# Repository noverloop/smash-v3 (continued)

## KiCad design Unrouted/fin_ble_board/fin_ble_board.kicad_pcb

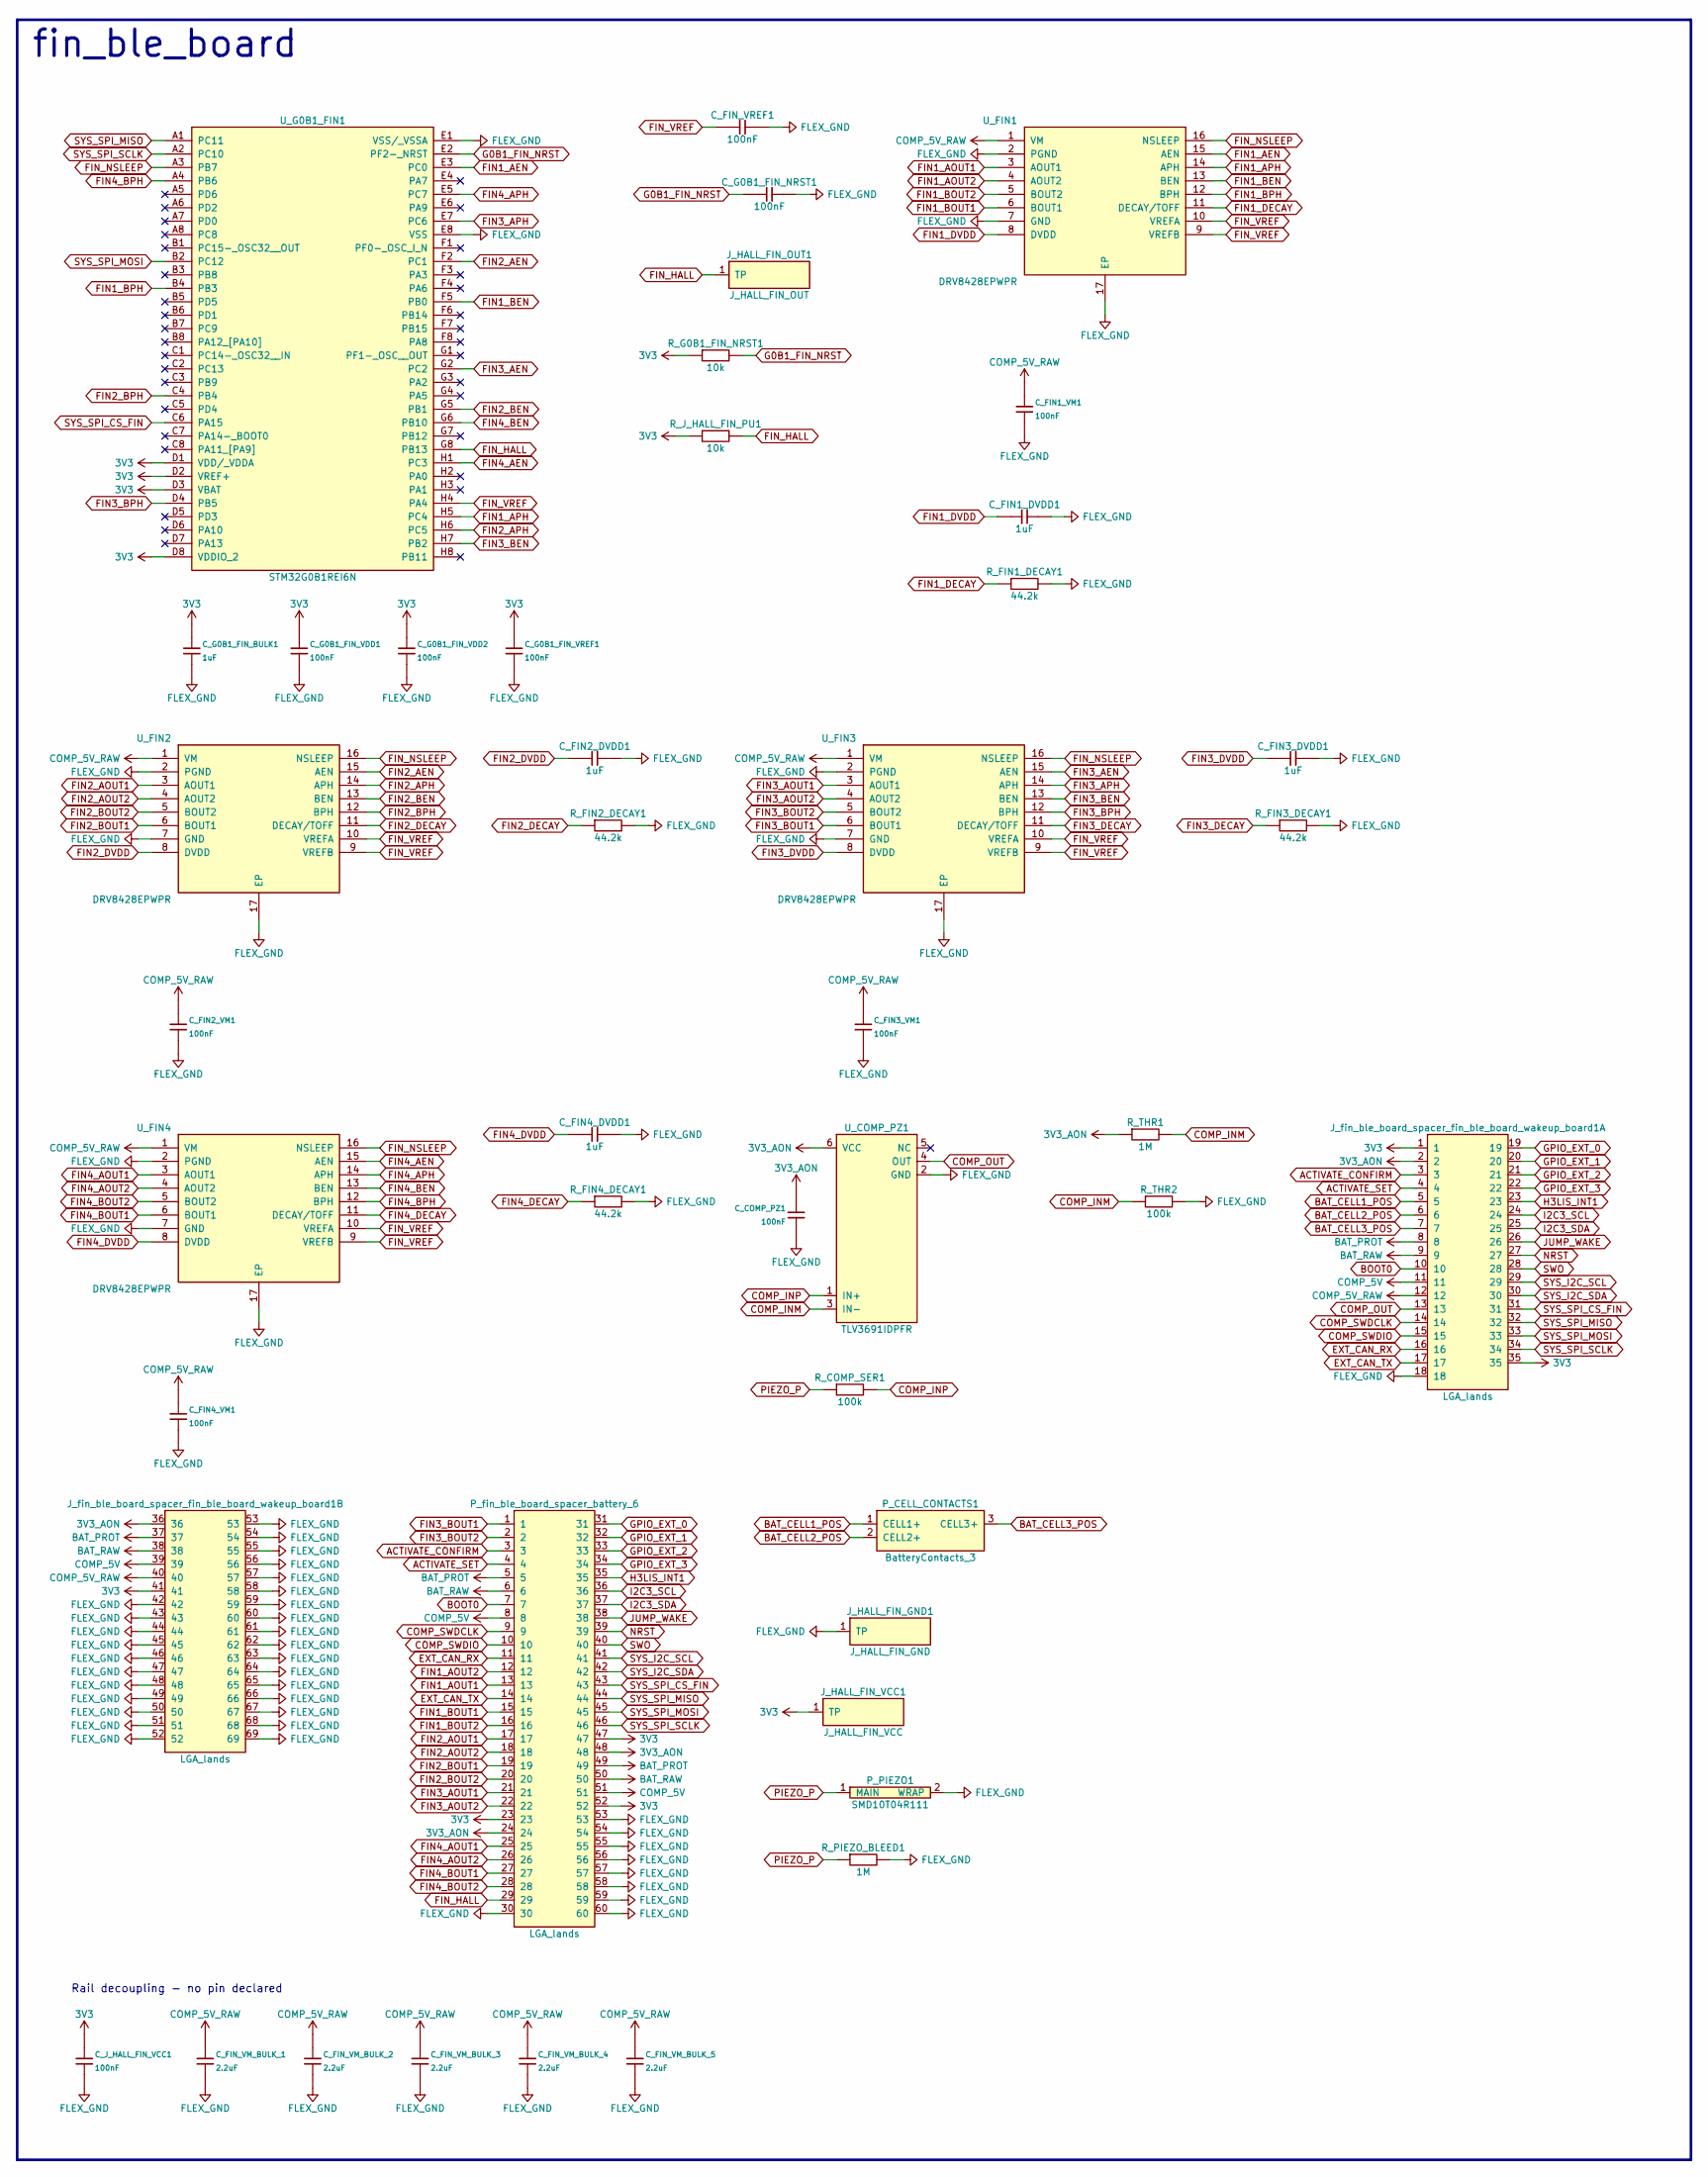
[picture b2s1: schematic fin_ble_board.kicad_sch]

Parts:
C_COMP_PZ1: 100nF; Capacitor_SMD_C_0402_1005Metric; MPN C0402 X7R 100nF
C_FIN1_DVDD1, C_FIN2_DVDD1, C_FIN3_DVDD1, C_FIN4_DVDD1: 1uF; Capacitor_SMD_C_0805_2012Metric; MPN C-Series MIL-PRF-32535 X7R 0805 1uF
C_FIN1_VM1, C_FIN2_VM1, C_FIN3_VM1, C_FIN4_VM1: 100nF; Capacitor_SMD_C_0402_1005Metric; MPN C0402 X7R 100nF
C_FIN_VM_BULK_1, C_FIN_VM_BULK_2, C_FIN_VM_BULK_3, C_FIN_VM_BULK_4, C_FIN_VM_BULK_5: 2.2uF; Capacitor_SMD_C_0603_1608Metric; MPN C-Series MIL-PRF-32535 X7R 0603 2.2uF
C_FIN_VREF1: 100nF; Capacitor_SMD_C_0402_1005Metric; MPN C0402 X7R 100nF
C_G0B1_FIN_BULK1: 1uF; Capacitor_SMD_C_0805_2012Metric; MPN C-Series MIL-PRF-32535 X7R 0805 1uF
C_G0B1_FIN_NRST1, C_G0B1_FIN_VDD1, C_G0B1_FIN_VDD2, C_G0B1_FIN_VREF1: 100nF; Capacitor_SMD_C_0402_1005Metric; MPN C0402 X7R 100nF
C_J_HALL_FIN_VCC1: 100nF; Capacitor_SMD_C_0402_1005Metric; MPN C0402 X7R 100nF
J_HALL_FIN_GND1: J_HALL_FIN_GND; Pogo_Pad_D2.0mm
J_HALL_FIN_OUT1: J_HALL_FIN_OUT; Pogo_Pad_D2.0mm
J_HALL_FIN_VCC1: J_HALL_FIN_VCC; Pogo_Pad_D2.0mm
J_fin_ble_board_spacer_fin_ble_board_wakeup_board1: LGA_lands; J_fin_ble_board_spacer_fin_ble_board_wakeup_board; MPN LGA_lands
P_CELL_CONTACTS1: BatteryContacts_3; MPN BatteryContacts_3
P_PIEZO1: SMD10T04R111; PiezoDisc_SMD10T04R111; MPN SMD10T04R111
P_fin_ble_board_spacer_battery_6: LGA_lands; P_fin_ble_board_spacer_battery_6; MPN LGA_lands
R_COMP_SER1: 100k; Resistor_SMD_R_0402_1005Metric; MPN CRCW0402 100k 1% e3
R_FIN1_DECAY1, R_FIN2_DECAY1, R_FIN3_DECAY1, R_FIN4_DECAY1: 44.2k; Resistor_SMD_R_0402_1005Metric; MPN CRCW0402 44.2k 1% e3
R_G0B1_FIN_NRST1: 10k; Resistor_SMD_R_0402_1005Metric; MPN CRCW0402 10k 1% e3
R_J_HALL_FIN_PU1: 10k; Resistor_SMD_R_0402_1005Metric; MPN CRCW0402 10k 1% e3
R_PIEZO_BLEED1: 1M; Resistor_SMD_R_0402_1005Metric; MPN CRCW0402 1M 1% e3
R_THR1: 1M; Resistor_SMD_R_0402_1005Metric; MPN CRCW0402 1M 1% e3
R_THR2: 100k; Resistor_SMD_R_0402_1005Metric; MPN CRCW0402 100k 1% e3
U_COMP_PZ1: TLV3691IDPFR; DPF0006A; MPN TLV3691IDPFR
U_FIN1, U_FIN2, U_FIN3, U_FIN4: DRV8428EPWPR; SOP65P640X120-17N; MPN DRV8428EPWPR
U_G0B1_FIN1: STM32G0B1REI6N; BGA64C50P8X8_500X500X60; MPN STM32G0B1REI6N

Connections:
3V3: C_G0B1_FIN_BULK1.1, C_G0B1_FIN_VDD1.1, C_G0B1_FIN_VDD2.1, C_G0B1_FIN_VREF1.1, C_J_HALL_FIN_VCC1.1, J_HALL_FIN_VCC1.1, J_fin_ble_board_spacer_fin_ble_board_wa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.1, J_fin_ble_board_spacer_fin_ble_board_wa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.35, J_fin_ble_board_spacer_fin_ble_board_wa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.41, P_fin_ble_board_spacer_battery_6.23, P_fin_ble_board_spacer_battery_6.47, P_fin_ble_board_spacer_battery_6.52, R_G0B1_FIN_NRST1.1, R_J_HALL_FIN_PU1.1, U_G0B1_FIN1.D1 (VDD/_VDDA), U_G0B1_FIN1.D2 (VREF+), U_G0B1_FIN1.D3 (VBAT), U_G0B1_FIN1.D8 (VDDIO_2)
3V3_AON: C_COMP_PZ1.1, J_fin_ble_board_spacer_fin_ble_board_wa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.2, J_fin_ble_board_spacer_fin_ble_board_wa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.36, P_fin_ble_board_spacer_battery_6.24, P_fin_ble_board_spacer_battery_6.48, R_THR1.1, U_COMP_PZ1.6 (VCC)
ACTIVATE_CONFIRM: J_fin_ble_board_spacer_fin_ble_board_wa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.3, P_fin_ble_board_spacer_battery_6.3
ACTIVATE_SET: J_fin_ble_board_spacer_fin_ble_board_wa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.4, P_fin_ble_board_spacer_battery_6.4
BAT_CELL1_POS: J_fin_ble_board_spacer_fin_ble_board_wa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.5, P_CELL_CONTACTS1.1 (CELL1+)
BAT_CELL2_POS: J_fin_ble_board_spacer_fin_ble_board_wa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.6, P_CELL_CONTACTS1.2 (CELL2+)
BAT_CELL3_POS: J_fin_ble_board_spacer_fin_ble_board_wa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.7, P_CELL_CONTACTS1.3 (CELL3+)
BAT_PROT: J_fin_ble_board_spacer_fin_ble_board_wa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.8, J_fin_ble_board_spacer_fin_ble_board_wa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.37, P_fin_ble_board_spacer_battery_6.5, P_fin_ble_board_spacer_battery_6.49
BAT_RAW: J_fin_ble_board_spacer_fin_ble_board_wa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.9, J_fin_ble_board_spacer_fin_ble_board_wa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.38, P_fin_ble_board_spacer_battery_6.6, P_fin_ble_board_spacer_battery_6.50
BOOT0: J_fin_ble_board_spacer_fin_ble_board_wa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.10, P_fin_ble_board_spacer_battery_6.7
COMP_5V: J_fin_ble_board_spacer_fin_ble_board_wa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.11, J_fin_ble_board_spacer_fin_ble_board_wa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.39, P_fin_ble_board_spacer_battery_6.8, P_fin_ble_board_spacer_battery_6.51
COMP_5V_RAW: C_FIN1_VM1.1, C_FIN2_VM1.1, C_FIN3_VM1.1, C_FIN4_VM1.1, C_FIN_VM_BULK_1.1, C_FIN_VM_BULK_2.1, C_FIN_VM_BULK_3.1, C_FIN_VM_BULK_4.1, C_FIN_VM_BULK_5.1, J_fin_ble_board_spacer_fin_ble_board_wa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.12, J_fin_ble_board_spacer_fin_ble_board_wa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.40, U_FIN1.1 (VM), U_FIN2.1 (VM), U_FIN3.1 (VM), U_FIN4.1 (VM)
COMP_INM: R_THR1.2, R_THR2.1, U_COMP_PZ1.3 (IN-)
COMP_INP: R_COMP_SER1.2, U_COMP_PZ1.1 (IN+)
COMP_OUT: J_fin_ble_board_spacer_fin_ble_board_wa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.13, U_COMP_PZ1.4 (OUT)
COMP_SWDCLK: J_fin_ble_board_spacer_fin_ble_board_wa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.14, P_fin_ble_board_spacer_battery_6.9
COMP_SWDIO: J_fin_ble_board_spacer_fin_ble_board_wa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.15, P_fin_ble_board_spacer_battery_6.10
EXT_CAN_RX: J_fin_ble_board_spacer_fin_ble_board_wa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.16, P_fin_ble_board_spacer_battery_6.11
EXT_CAN_TX: J_fin_ble_board_spacer_fin_ble_board_wa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.17, P_fin_ble_board_spacer_battery_6.14
FIN1_AEN: U_FIN1.15 (AEN), U_G0B1_FIN1.E3 (PC0)
FIN1_AOUT1: P_fin_ble_board_spacer_battery_6.13, U_FIN1.3 (AOUT1)
FIN1_AOUT2: P_fin_ble_board_spacer_battery_6.12, U_FIN1.4 (AOUT2)
FIN1_APH: U_FIN1.14 (APH), U_G0B1_FIN1.H5 (PC4)
FIN1_BEN: U_FIN1.13 (BEN), U_G0B1_FIN1.F5 (PB0)
FIN1_BOUT1: P_fin_ble_board_spacer_battery_6.15, U_FIN1.6 (BOUT1)
FIN1_BOUT2: P_fin_ble_board_spacer_battery_6.16, U_FIN1.5 (BOUT2)
FIN1_BPH: U_FIN1.12 (BPH), U_G0B1_FIN1.B4 (PB3)
FIN1_DECAY: R_FIN1_DECAY1.1, U_FIN1.11 (DECAY/TOFF)
FIN1_DVDD: C_FIN1_DVDD1.1, U_FIN1.8 (DVDD)
FIN2_AEN: U_FIN2.15 (AEN), U_G0B1_FIN1.F2 (PC1)
FIN2_AOUT1: P_fin_ble_board_spacer_battery_6.17, U_FIN2.3 (AOUT1)
FIN2_AOUT2: P_fin_ble_board_spacer_battery_6.18, U_FIN2.4 (AOUT2)
FIN2_APH: U_FIN2.14 (APH), U_G0B1_FIN1.H6 (PC5)
FIN2_BEN: U_FIN2.13 (BEN), U_G0B1_FIN1.G5 (PB1)
FIN2_BOUT1: P_fin_ble_board_spacer_battery_6.19, U_FIN2.6 (BOUT1)
FIN2_BOUT2: P_fin_ble_board_spacer_battery_6.20, U_FIN2.5 (BOUT2)
FIN2_BPH: U_FIN2.12 (BPH), U_G0B1_FIN1.C4 (PB4)
FIN2_DECAY: R_FIN2_DECAY1.1, U_FIN2.11 (DECAY/TOFF)
FIN2_DVDD: C_FIN2_DVDD1.1, U_FIN2.8 (DVDD)
FIN3_AEN: U_FIN3.15 (AEN), U_G0B1_FIN1.G2 (PC2)
FIN3_AOUT1: P_fin_ble_board_spacer_battery_6.21, U_FIN3.3 (AOUT1)
FIN3_AOUT2: P_fin_ble_board_spacer_battery_6.22, U_FIN3.4 (AOUT2)
FIN3_APH: U_FIN3.14 (APH), U_G0B1_FIN1.E7 (PC6)
FIN3_BEN: U_FIN3.13 (BEN), U_G0B1_FIN1.H7 (PB2)
FIN3_BOUT1: P_fin_ble_board_spacer_battery_6.1, U_FIN3.6 (BOUT1)
FIN3_BOUT2: P_fin_ble_board_spacer_battery_6.2, U_FIN3.5 (BOUT2)
FIN3_BPH: U_FIN3.12 (BPH), U_G0B1_FIN1.D4 (PB5)
FIN3_DECAY: R_FIN3_DECAY1.1, U_FIN3.11 (DECAY/TOFF)
FIN3_DVDD: C_FIN3_DVDD1.1, U_FIN3.8 (DVDD)
FIN4_AEN: U_FIN4.15 (AEN), U_G0B1_FIN1.H1 (PC3)
FIN4_AOUT1: P_fin_ble_board_spacer_battery_6.25, U_FIN4.3 (AOUT1)
FIN4_AOUT2: P_fin_ble_board_spacer_battery_6.26, U_FIN4.4 (AOUT2)
FIN4_APH: U_FIN4.14 (APH), U_G0B1_FIN1.E5 (PC7)
FIN4_BEN: U_FIN4.13 (BEN), U_G0B1_FIN1.G6 (PB10)
FIN4_BOUT1: P_fin_ble_board_spacer_battery_6.27, U_FIN4.6 (BOUT1)
FIN4_BOUT2: P_fin_ble_board_spacer_battery_6.28, U_FIN4.5 (BOUT2)
FIN4_BPH: U_FIN4.12 (BPH), U_G0B1_FIN1.A4 (PB6)
FIN4_DECAY: R_FIN4_DECAY1.1, U_FIN4.11 (DECAY/TOFF)
FIN4_DVDD: C_FIN4_DVDD1.1, U_FIN4.8 (DVDD)
FIN_HALL: J_HALL_FIN_OUT1.1, P_fin_ble_board_spacer_battery_6.29, R_J_HALL_FIN_PU1.2, U_G0B1_FIN1.G8 (PB13)
FIN_NSLEEP: U_FIN1.16 (NSLEEP), U_FIN2.16 (NSLEEP), U_FIN3.16 (NSLEEP), U_FIN4.16 (NSLEEP), U_G0B1_FIN1.A3 (PB7)
FIN_VREF: C_FIN_VREF1.1, U_FIN1.9 (VREFB), U_FIN1.10 (VREFA), U_FIN2.9 (VREFB), U_FIN2.10 (VREFA), U_FIN3.9 (VREFB), U_FIN3.10 (VREFA), U_FIN4.9 (VREFB), U_FIN4.10 (VREFA), U_G0B1_FIN1.H4 (PA4)
FLEX_GND: C_COMP_PZ1.2, C_FIN1_DVDD1.2, C_FIN1_VM1.2, C_FIN2_DVDD1.2, C_FIN2_VM1.2, C_FIN3_DVDD1.2, C_FIN3_VM1.2, C_FIN4_DVDD1.2, C_FIN4_VM1.2, C_FIN_VM_BULK_1.2, C_FIN_VM_BULK_2.2, C_FIN_VM_BULK_3.2, C_FIN_VM_BULK_4.2, C_FIN_VM_BULK_5.2, C_FIN_VREF1.2, C_G0B1_FIN_BULK1.2, C_G0B1_FIN_NRST1.2, C_G0B1_FIN_VDD1.2, C_G0B1_FIN_VDD2.2, C_G0B1_FIN_VREF1.2, C_J_HALL_FIN_VCC1.2, J_HALL_FIN_GND1.1, J_fin_ble_board_spacer_fin_ble_board_wa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.18, J_fin_ble_board_spacer_fin_ble_board_wa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.42, J_fin_ble_board_spacer_fin_ble_board_wa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.43, J_fin_ble_board_spacer_fin_ble_board_wa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.44, J_fin_ble_board_spacer_fin_ble_board_wa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.45, J_fin_ble_board_spacer_fin_ble_board_wa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.46, J_fin_ble_board_spacer_fin_ble_board_wa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.47, J_fin_ble_board_spacer_fin_ble_board_wa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.48, J_fin_ble_board_spacer_fin_ble_board_wa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.49, J_fin_ble_board_spacer_fin_ble_board_wa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.50, J_fin_ble_board_spacer_fin_ble_board_wa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.51, J_fin_ble_board_spacer_fin_ble_board_wa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.52, J_fin_ble_board_spacer_fin_ble_board_wa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.53, J_fin_ble_board_spacer_fin_ble_board_wa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.54, J_fin_ble_board_spacer_fin_ble_board_wa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.55, J_fin_ble_board_spacer_fin_ble_board_wa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.56, J_fin_ble_board_spacer_fin_ble_board_wa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.57, J_fin_ble_board_spacer_fin_ble_board_wa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.58, J_fin_ble_board_spacer_fin_ble_board_wa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.59, J_fin_ble_board_spacer_fin_ble_board_wa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.60, J_fin_ble_board_spacer_fin_ble_board_wa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.61, J_fin_ble_board_spacer_fin_ble_board_wa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.62, J_fin_ble_board_spacer_fin_ble_board_wa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.63, J_fin_ble_board_spacer_fin_ble_board_wa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.64, J_fin_ble_board_spacer_fin_ble_board_wa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.65, J_fin_ble_board_spacer_fin_ble_board_wa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.66, J_fin_ble_board_spacer_fin_ble_board_wa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.67, J_fin_ble_board_spacer_fin_ble_board_wa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.68, J_fin_ble_board_spacer_fin_ble_board_wa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.69, P_PIEZO1.2 (WRAP), P_fin_ble_board_spacer_battery_6.30, P_fin_ble_board_spacer_battery_6.53, P_fin_ble_board_spacer_battery_6.54, P_fin_ble_board_spacer_battery_6.55, P_fin_ble_board_spacer_battery_6.56, P_fin_ble_board_spacer_battery_6.57, P_fin_ble_board_spacer_battery_6.58, P_fin_ble_board_spacer_battery_6.59, P_fin_ble_board_spacer_battery_6.60, R_FIN1_DECAY1.2, R_FIN2_DECAY1.2, R_FIN3_DECAY1.2, R_FIN4_DECAY1.2, R_PIEZO_BLEED1.2, R_THR2.2, U_COMP_PZ1.2 (GND), U_FIN1.2 (PGND), U_FIN1.7 (GND), U_FIN1.17 (EP), U_FIN2.2 (PGND), U_FIN2.7 (GND), U_FIN2.17 (EP), U_FIN3.2 (PGND), U_FIN3.7 (GND), U_FIN3.17 (EP), U_FIN4.2 (PGND), U_FIN4.7 (GND), U_FIN4.17 (EP), U_G0B1_FIN1.E1 (VSS/_VSSA), U_G0B1_FIN1.E8 (VSS)
G0B1_FIN_NRST: C_G0B1_FIN_NRST1.1, R_G0B1_FIN_NRST1.2, U_G0B1_FIN1.E2 (PF2-_NRST)
GPIO_EXT_0: J_fin_ble_board_spacer_fin_ble_board_wa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.19, P_fin_ble_board_spacer_battery_6.31
GPIO_EXT_1: J_fin_ble_board_spacer_fin_ble_board_wa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.20, P_fin_ble_board_spacer_battery_6.32
GPIO_EXT_2: J_fin_ble_board_spacer_fin_ble_board_wa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.21, P_fin_ble_board_spacer_battery_6.33
GPIO_EXT_3: J_fin_ble_board_spacer_fin_ble_board_wa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.22, P_fin_ble_board_spacer_battery_6.34
H3LIS_INT1: J_fin_ble_board_spacer_fin_ble_board_wa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.23, P_fin_ble_board_spacer_battery_6.35
I2C3_SCL: J_fin_ble_board_spacer_fin_ble_board_wa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.24, P_fin_ble_board_spacer_battery_6.36
I2C3_SDA: J_fin_ble_board_spacer_fin_ble_board_wa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.25, P_fin_ble_board_spacer_battery_6.37
JUMP_WAKE: J_fin_ble_board_spacer_fin_ble_board_wa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.26, P_fin_ble_board_spacer_battery_6.38
NRST: J_fin_ble_board_spacer_fin_ble_board_wa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.27, P_fin_ble_board_spacer_battery_6.39
PIEZO_P: P_PIEZO1.1 (MAIN), R_COMP_SER1.1, R_PIEZO_BLEED1.1
SWO: J_fin_ble_board_spacer_fin_ble_board_wa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.28, P_fin_ble_board_spacer_battery_6.40
SYS_I2C_SCL: J_fin_ble_board_spacer_fin_ble_board_wa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.29, P_fin_ble_board_spacer_battery_6.41
SYS_I2C_SDA: J_fin_ble_board_spacer_fin_ble_board_wa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.30, P_fin_ble_board_spacer_battery_6.42
SYS_SPI_CS_FIN: J_fin_ble_board_spacer_fin_ble_board_wa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.31, P_fin_ble_board_spacer_battery_6.43, U_G0B1_FIN1.C6 (PA15)
SYS_SPI_MISO: J_fin_ble_board_spacer_fin_ble_board_wa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.32, P_fin_ble_board_spacer_battery_6.44, U_G0B1_FIN1.A1 (PC11)
SYS_SPI_MOSI: J_fin_ble_board_spacer_fin_ble_board_wa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.33, P_fin_ble_board_spacer_battery_6.45, U_G0B1_FIN1.B2 (PC12)
SYS_SPI_SCLK: J_fin_ble_board_spacer_fin_ble_board_wa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.34, P_fin_ble_board_spacer_battery_6.46, U_G0B1_FIN1.A2 (PC10)

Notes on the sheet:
fin_ble_board
Rail decoupling - no pin declared

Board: 14 copper layers, 46 parts (31 on the bottom side), 81 nets, no tracks yet.

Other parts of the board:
MH1, MH2: smash_mech_potting

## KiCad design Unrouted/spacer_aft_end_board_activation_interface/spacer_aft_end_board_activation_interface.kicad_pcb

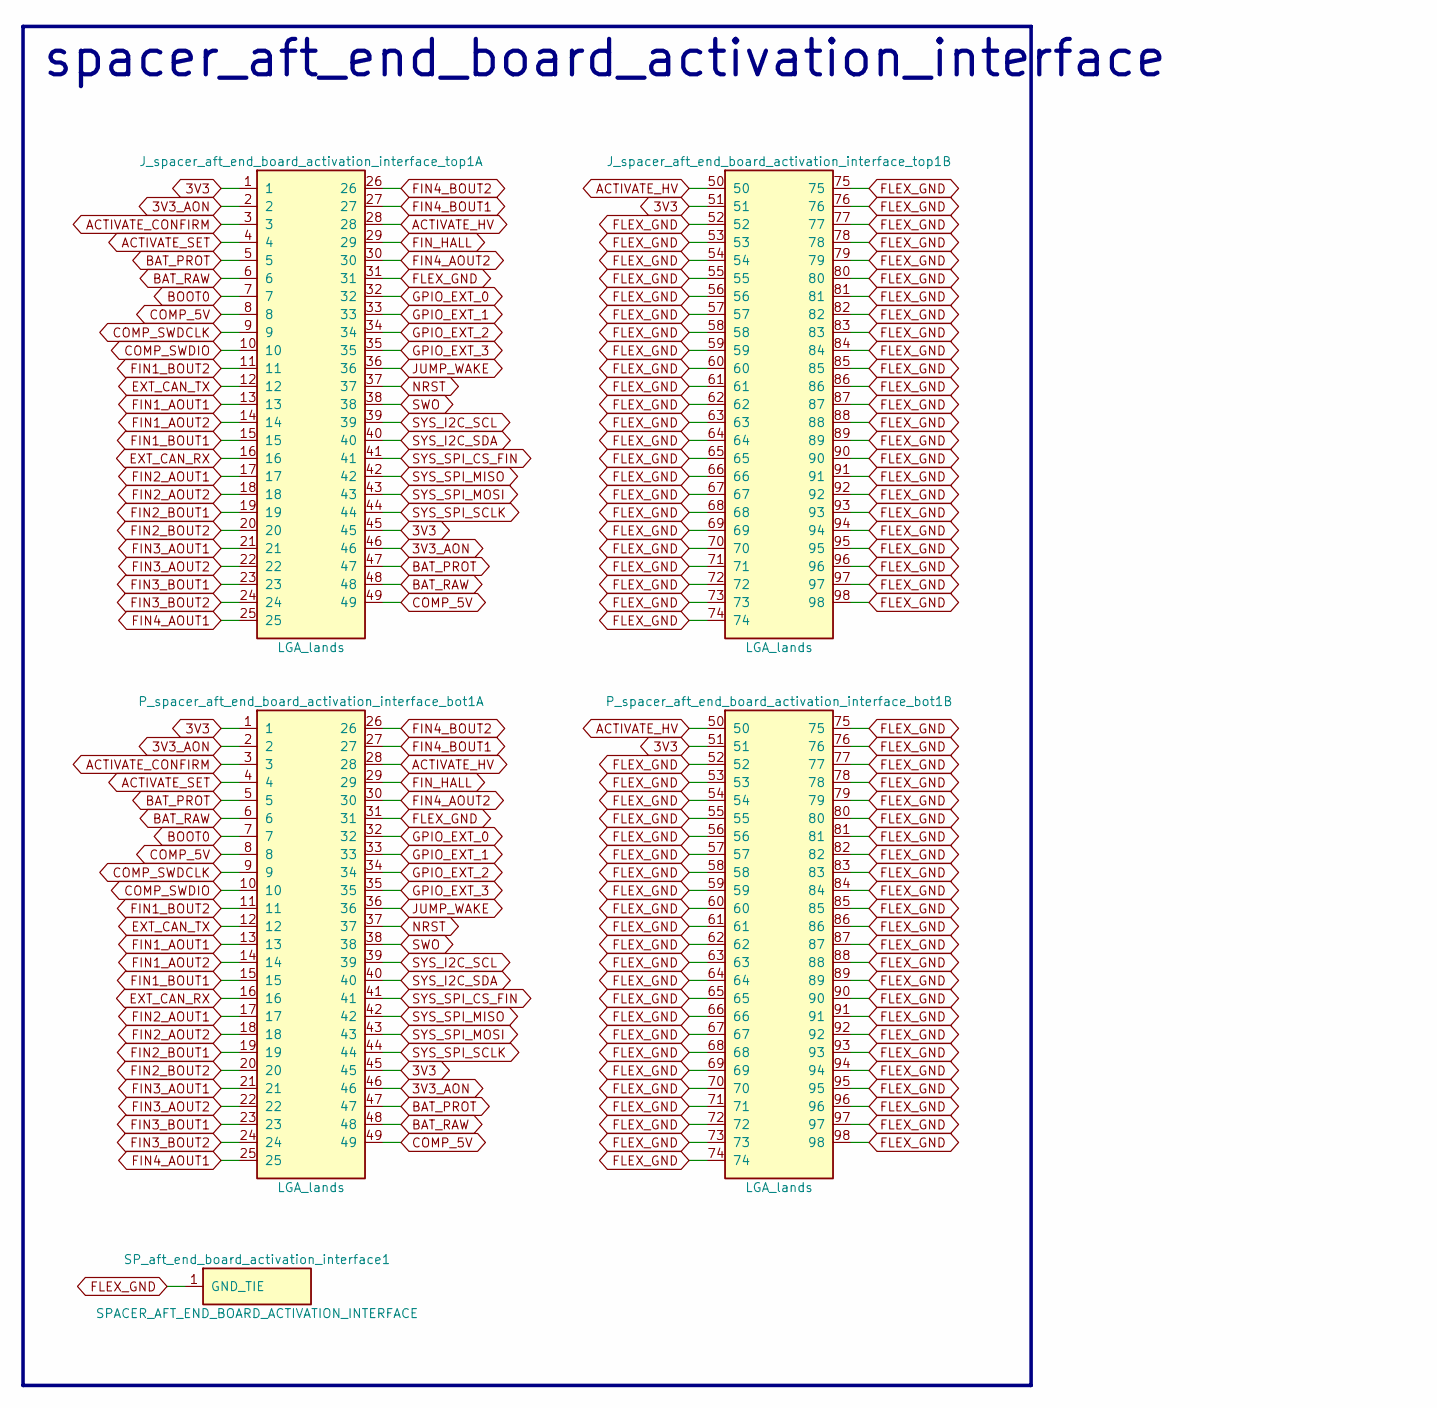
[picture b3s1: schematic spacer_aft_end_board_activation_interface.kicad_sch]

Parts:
J_spacer_aft_end_board_activation_interface_top1: LGA_lands; J_spacer_aft_end_board_activation_interface_top; MPN LGA_lands
P_spacer_aft_end_board_activation_interface_bot1: LGA_lands; P_spacer_aft_end_board_activation_interface_bot; MPN LGA_lands
SP_aft_end_board_activation_interface1: SPACER_AFT_END_BOARD_ACTIVATION_INTERFACE; Spacer_Mechanical_34mm

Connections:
3V3: J_spacer_aft_end_board_activation_inter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.1, J_spacer_aft_end_board_activation_inter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.45, J_spacer_aft_end_board_activation_inter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.51, P_spacer_aft_end_board_activation_inter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.1, P_spacer_aft_end_board_activation_inter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.45, P_spacer_aft_end_board_activation_inter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.51
3V3_AON: J_spacer_aft_end_board_activation_inter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.2, J_spacer_aft_end_board_activation_inter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.46, P_spacer_aft_end_board_activation_inter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.2, P_spacer_aft_end_board_activation_inter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.46
ACTIVATE_CONFIRM: J_spacer_aft_end_board_activation_inter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.3, P_spacer_aft_end_board_activation_inter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.3
ACTIVATE_HV: J_spacer_aft_end_board_activation_inter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.28, J_spacer_aft_end_board_activation_inter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.50, P_spacer_aft_end_board_activation_inter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.28, P_spacer_aft_end_board_activation_inter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.50
ACTIVATE_SET: J_spacer_aft_end_board_activation_inter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.4, P_spacer_aft_end_board_activation_inter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.4
BAT_PROT: J_spacer_aft_end_board_activation_inter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.5, J_spacer_aft_end_board_activation_inter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.47, P_spacer_aft_end_board_activation_inter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.5, P_spacer_aft_end_board_activation_inter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.47
BAT_RAW: J_spacer_aft_end_board_activation_inter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.6, J_spacer_aft_end_board_activation_inter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.48, P_spacer_aft_end_board_activation_inter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.6, P_spacer_aft_end_board_activation_inter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.48
BOOT0: J_spacer_aft_end_board_activation_inter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.7, P_spacer_aft_end_board_activation_inter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.7
COMP_5V: J_spacer_aft_end_board_activation_inter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.8, J_spacer_aft_end_board_activation_inter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.49, P_spacer_aft_end_board_activation_inter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.8, P_spacer_aft_end_board_activation_inter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.49
COMP_SWDCLK: J_spacer_aft_end_board_activation_inter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.9, P_spacer_aft_end_board_activation_inter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.9
COMP_SWDIO: J_spacer_aft_end_board_activation_inter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.10, P_spacer_aft_end_board_activation_inter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.10
EXT_CAN_RX: J_spacer_aft_end_board_activation_inter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.16, P_spacer_aft_end_board_activation_inter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.16
EXT_CAN_TX: J_spacer_aft_end_board_activation_inter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.12, P_spacer_aft_end_board_activation_inter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.12
FIN1_AOUT1: J_spacer_aft_end_board_activation_inter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.13, P_spacer_aft_end_board_activation_inter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.13
FIN1_AOUT2: J_spacer_aft_end_board_activation_inter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.14, P_spacer_aft_end_board_activation_inter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.14
FIN1_BOUT1: J_spacer_aft_end_board_activation_inter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.15, P_spacer_aft_end_board_activation_inter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.15
FIN1_BOUT2: J_spacer_aft_end_board_activation_inter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.11, P_spacer_aft_end_board_activation_inter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.11
FIN2_AOUT1: J_spacer_aft_end_board_activation_inter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.17, P_spacer_aft_end_board_activation_inter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.17
FIN2_AOUT2: J_spacer_aft_end_board_activation_inter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.18, P_spacer_aft_end_board_activation_inter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.18
FIN2_BOUT1: J_spacer_aft_end_board_activation_inter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.19, P_spacer_aft_end_board_activation_inter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.19
FIN2_BOUT2: J_spacer_aft_end_board_activation_inter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.20, P_spacer_aft_end_board_activation_inter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.20
FIN3_AOUT1: J_spacer_aft_end_board_activation_inter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.21, P_spacer_aft_end_board_activation_inter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.21
FIN3_AOUT2: J_spacer_aft_end_board_activation_inter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.22, P_spacer_aft_end_board_activation_inter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.22
FIN3_BOUT1: J_spacer_aft_end_board_activation_inter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.23, P_spacer_aft_end_board_activation_inter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.23
FIN3_BOUT2: J_spacer_aft_end_board_activation_inter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.24, P_spacer_aft_end_board_activation_inter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.24
FIN4_AOUT1: J_spacer_aft_end_board_activation_inter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.25, P_spacer_aft_end_board_activation_inter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.25
FIN4_AOUT2: J_spacer_aft_end_board_activation_inter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.30, P_spacer_aft_end_board_activation_inter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.30
FIN4_BOUT1: J_spacer_aft_end_board_activation_inter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.27, P_spacer_aft_end_board_activation_inter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.27
FIN4_BOUT2: J_spacer_aft_end_board_activation_inter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.26, P_spacer_aft_end_board_activation_inter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.26
FIN_HALL: J_spacer_aft_end_board_activation_inter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.29, P_spacer_aft_end_board_activation_inter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.29
FLEX_GND: J_spacer_aft_end_board_activation_inter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.31, J_spacer_aft_end_board_activation_inter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.52, J_spacer_aft_end_board_activation_inter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.53, J_spacer_aft_end_board_activation_inter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.54, J_spacer_aft_end_board_activation_inter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.55, J_spacer_aft_end_board_activation_inter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.56, J_spacer_aft_end_board_activation_inter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.57, J_spacer_aft_end_board_activation_inter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.58, J_spacer_aft_end_board_activation_inter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.59, J_spacer_aft_end_board_activation_inter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.60, J_spacer_aft_end_board_activation_inter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.61, J_spacer_aft_end_board_activation_inter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.62, J_spacer_aft_end_board_activation_inter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.63, J_spacer_aft_end_board_activation_inter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.64, J_spacer_aft_end_board_activation_inter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.65, J_spacer_aft_end_board_activation_inter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.66, J_spacer_aft_end_board_activation_inter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.67, J_spacer_aft_end_board_activation_inter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.68, J_spacer_aft_end_board_activation_inter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.69, J_spacer_aft_end_board_activation_inter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.70, J_spacer_aft_end_board_activation_inter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.71, J_spacer_aft_end_board_activation_inter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.72, J_spacer_aft_end_board_activation_inter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.73, J_spacer_aft_end_board_activation_inter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.74, J_spacer_aft_end_board_activation_inter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.75, J_spacer_aft_end_board_activation_inter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.76, J_spacer_aft_end_board_activation_inter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.77, J_spacer_aft_end_board_activation_inter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.78, J_spacer_aft_end_board_activation_inter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.79, J_spacer_aft_end_board_activation_inter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.80, J_spacer_aft_end_board_activation_inter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.81, J_spacer_aft_end_board_activation_inter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.82, J_spacer_aft_end_board_activation_inter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.83, J_spacer_aft_end_board_activation_inter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.84, J_spacer_aft_end_board_activation_inter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.85, J_spacer_aft_end_board_activation_inter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.86, J_spacer_aft_end_board_activation_inter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.87, J_spacer_aft_end_board_activation_inter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.88, J_spacer_aft_end_board_activation_inter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.89, J_spacer_aft_end_board_activation_inter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.90, J_spacer_aft_end_board_activation_inter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.91, J_spacer_aft_end_board_activation_inter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.92, J_spacer_aft_end_board_activation_inter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.93, J_spacer_aft_end_board_activation_inter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.94, J_spacer_aft_end_board_activation_inter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.95, J_spacer_aft_end_board_activation_inter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.96, J_spacer_aft_end_board_activation_inter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.97, J_spacer_aft_end_board_activation_inter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.98, P_spacer_aft_end_board_activation_inter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.31, P_spacer_aft_end_board_activation_inter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.52, P_spacer_aft_end_board_activation_inter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.53, P_spacer_aft_end_board_activation_inter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.54, P_spacer_aft_end_board_activation_inter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.55, P_spacer_aft_end_board_activation_inter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.56, P_spacer_aft_end_board_activation_inter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.57, P_spacer_aft_end_board_activation_inter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.58, P_spacer_aft_end_board_activation_inter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.59, P_spacer_aft_end_board_activation_inter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.60, P_spacer_aft_end_board_activation_inter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.61, P_spacer_aft_end_board_activation_inter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.62, P_spacer_aft_end_board_activation_inter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.63, P_spacer_aft_end_board_activation_inter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.64, P_spacer_aft_end_board_activation_inter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.65, P_spacer_aft_end_board_activation_inter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.66, P_spacer_aft_end_board_activation_inter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.67, P_spacer_aft_end_board_activation_inter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.68, P_spacer_aft_end_board_activation_inter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.69, P_spacer_aft_end_board_activation_inter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.70, P_spacer_aft_end_board_activation_inter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.71, P_spacer_aft_end_board_activation_inter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.72, P_spacer_aft_end_board_activation_inter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.73, P_spacer_aft_end_board_activation_inter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.74, P_spacer_aft_end_board_activation_inter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.75, P_spacer_aft_end_board_activation_inter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.76, P_spacer_aft_end_board_activation_inter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.77, P_spacer_aft_end_board_activation_inter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.78, P_spacer_aft_end_board_activation_inter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.79, P_spacer_aft_end_board_activation_inter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.80, P_spacer_aft_end_board_activation_inter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.81, P_spacer_aft_end_board_activation_inter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.82, P_spacer_aft_end_board_activation_inter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.83, P_spacer_aft_end_board_activation_inter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.84, P_spacer_aft_end_board_activation_inter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.85, P_spacer_aft_end_board_activation_inter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.86, P_spacer_aft_end_board_activation_inter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.87, P_spacer_aft_end_board_activation_inter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.88, P_spacer_aft_end_board_activation_inter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.89, P_spacer_aft_end_board_activation_inter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.90, P_spacer_aft_end_board_activation_inter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.91, P_spacer_aft_end_board_activation_inter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.92, P_spacer_aft_end_board_activation_inter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.93, P_spacer_aft_end_board_activation_inter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.94, P_spacer_aft_end_board_activation_inter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.95, P_spacer_aft_end_board_activation_inter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.96, P_spacer_aft_end_board_activation_inter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.97, P_spacer_aft_end_board_activation_inter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.98, SP_aft_end_board_activation_interface1.1
GPIO_EXT_0: J_spacer_aft_end_board_activation_inter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.32, P_spacer_aft_end_board_activation_inter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.32
GPIO_EXT_1: J_spacer_aft_end_board_activation_inter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.33, P_spacer_aft_end_board_activation_inter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.33
GPIO_EXT_2: J_spacer_aft_end_board_activation_inter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.34, P_spacer_aft_end_board_activation_inter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.34
GPIO_EXT_3: J_spacer_aft_end_board_activation_inter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.35, P_spacer_aft_end_board_activation_inter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.35
JUMP_WAKE: J_spacer_aft_end_board_activation_inter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.36, P_spacer_aft_end_board_activation_inter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.36
NRST: J_spacer_aft_end_board_activation_inter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.37, P_spacer_aft_end_board_activation_inter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.37
SWO: J_spacer_aft_end_board_activation_inter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.38, P_spacer_aft_end_board_activation_inter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.38
SYS_I2C_SCL: J_spacer_aft_end_board_activation_inter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.39, P_spacer_aft_end_board_activation_inter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.39
SYS_I2C_SDA: J_spacer_aft_end_board_activation_inter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.40, P_spacer_aft_end_board_activation_inter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.40
SYS_SPI_CS_FIN: J_spacer_aft_end_board_activation_inter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.41, P_spacer_aft_end_board_activation_inter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.41
SYS_SPI_MISO: J_spacer_aft_end_board_activation_inter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.42, P_spacer_aft_end_board_activation_inter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.42
SYS_SPI_MOSI: J_spacer_aft_end_board_activation_inter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.43, P_spacer_aft_end_board_activation_inter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.43
SYS_SPI_SCLK: J_spacer_aft_end_board_activation_inter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.44, P_spacer_aft_end_board_activation_inter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.44

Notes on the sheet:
spacer_aft_end_board_activation_interface

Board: 2 copper layers, 5 parts (1 on the bottom side), 44 nets, no tracks yet.

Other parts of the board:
MH1, MH2: smash_mech_potting

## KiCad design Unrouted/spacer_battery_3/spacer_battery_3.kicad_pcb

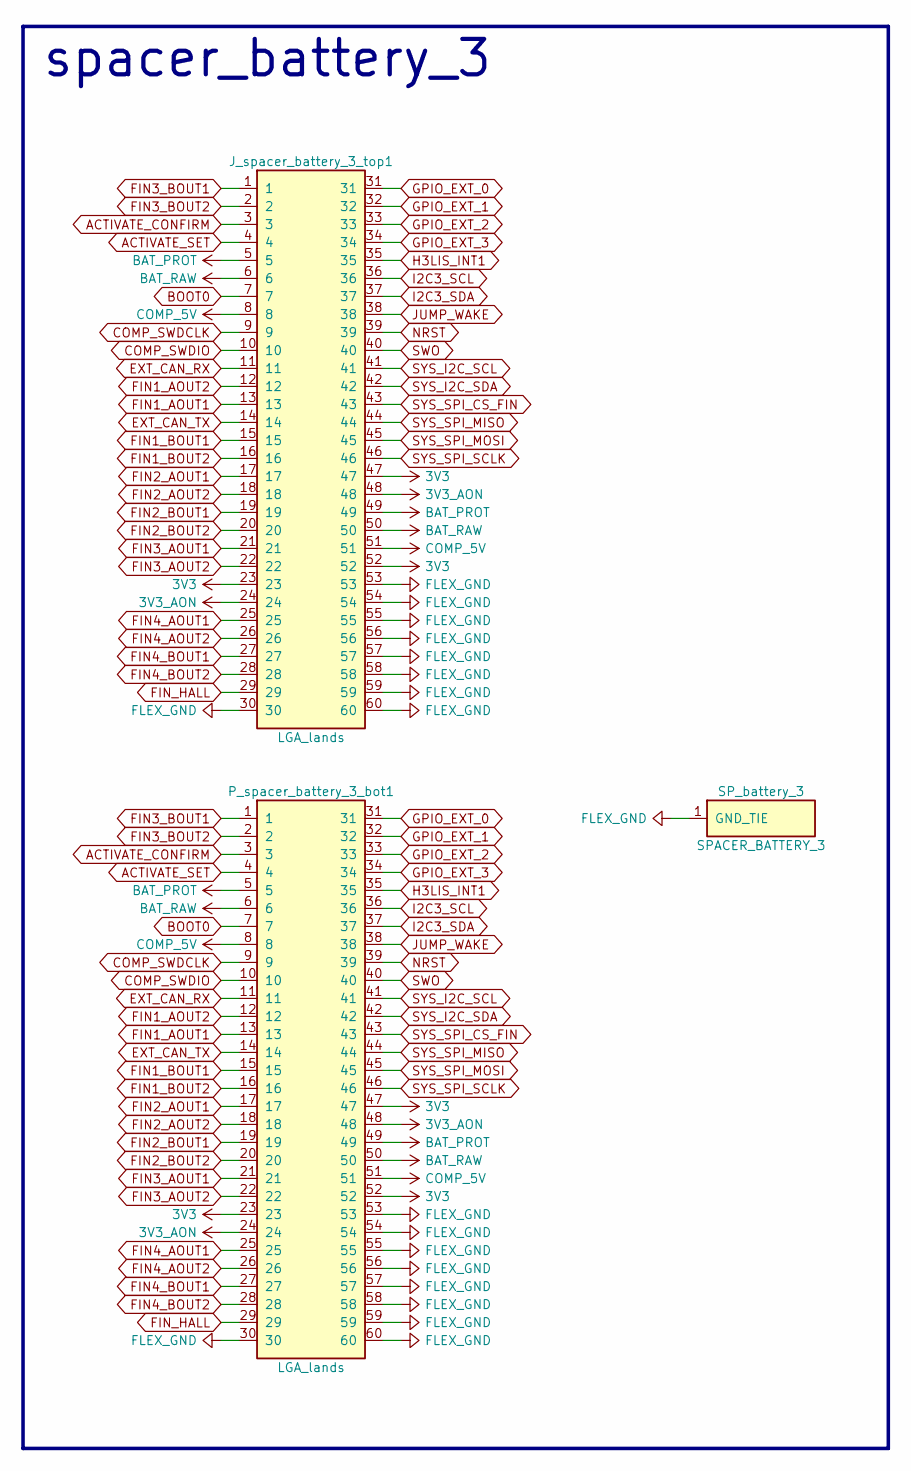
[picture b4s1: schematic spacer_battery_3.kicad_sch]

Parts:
J_spacer_battery_3_top1: LGA_lands; J_spacer_battery_3_top; MPN LGA_lands
P_spacer_battery_3_bot1: LGA_lands; P_spacer_battery_3_bot; MPN LGA_lands
SP_battery_3: SPACER_BATTERY_3; Spacer_Mechanical_34mm

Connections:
3V3: J_spacer_battery_3_top1.23, J_spacer_battery_3_top1.47, J_spacer_battery_3_top1.52, P_spacer_battery_3_bot1.23, P_spacer_battery_3_bot1.47, P_spacer_battery_3_bot1.52
3V3_AON: J_spacer_battery_3_top1.24, J_spacer_battery_3_top1.48, P_spacer_battery_3_bot1.24, P_spacer_battery_3_bot1.48
ACTIVATE_CONFIRM: J_spacer_battery_3_top1.3, P_spacer_battery_3_bot1.3
ACTIVATE_SET: J_spacer_battery_3_top1.4, P_spacer_battery_3_bot1.4
BAT_PROT: J_spacer_battery_3_top1.5, J_spacer_battery_3_top1.49, P_spacer_battery_3_bot1.5, P_spacer_battery_3_bot1.49
BAT_RAW: J_spacer_battery_3_top1.6, J_spacer_battery_3_top1.50, P_spacer_battery_3_bot1.6, P_spacer_battery_3_bot1.50
BOOT0: J_spacer_battery_3_top1.7, P_spacer_battery_3_bot1.7
COMP_5V: J_spacer_battery_3_top1.8, J_spacer_battery_3_top1.51, P_spacer_battery_3_bot1.8, P_spacer_battery_3_bot1.51
COMP_SWDCLK: J_spacer_battery_3_top1.9, P_spacer_battery_3_bot1.9
COMP_SWDIO: J_spacer_battery_3_top1.10, P_spacer_battery_3_bot1.10
EXT_CAN_RX: J_spacer_battery_3_top1.11, P_spacer_battery_3_bot1.11
EXT_CAN_TX: J_spacer_battery_3_top1.14, P_spacer_battery_3_bot1.14
FIN1_AOUT1: J_spacer_battery_3_top1.13, P_spacer_battery_3_bot1.13
FIN1_AOUT2: J_spacer_battery_3_top1.12, P_spacer_battery_3_bot1.12
FIN1_BOUT1: J_spacer_battery_3_top1.15, P_spacer_battery_3_bot1.15
FIN1_BOUT2: J_spacer_battery_3_top1.16, P_spacer_battery_3_bot1.16
FIN2_AOUT1: J_spacer_battery_3_top1.17, P_spacer_battery_3_bot1.17
FIN2_AOUT2: J_spacer_battery_3_top1.18, P_spacer_battery_3_bot1.18
FIN2_BOUT1: J_spacer_battery_3_top1.19, P_spacer_battery_3_bot1.19
FIN2_BOUT2: J_spacer_battery_3_top1.20, P_spacer_battery_3_bot1.20
FIN3_AOUT1: J_spacer_battery_3_top1.21, P_spacer_battery_3_bot1.21
FIN3_AOUT2: J_spacer_battery_3_top1.22, P_spacer_battery_3_bot1.22
FIN3_BOUT1: J_spacer_battery_3_top1.1, P_spacer_battery_3_bot1.1
FIN3_BOUT2: J_spacer_battery_3_top1.2, P_spacer_battery_3_bot1.2
FIN4_AOUT1: J_spacer_battery_3_top1.25, P_spacer_battery_3_bot1.25
FIN4_AOUT2: J_spacer_battery_3_top1.26, P_spacer_battery_3_bot1.26
FIN4_BOUT1: J_spacer_battery_3_top1.27, P_spacer_battery_3_bot1.27
FIN4_BOUT2: J_spacer_battery_3_top1.28, P_spacer_battery_3_bot1.28
FIN_HALL: J_spacer_battery_3_top1.29, P_spacer_battery_3_bot1.29
FLEX_GND: J_spacer_battery_3_top1.30, J_spacer_battery_3_top1.53, J_spacer_battery_3_top1.54, J_spacer_battery_3_top1.55, J_spacer_battery_3_top1.56, J_spacer_battery_3_top1.57, J_spacer_battery_3_top1.58, J_spacer_battery_3_top1.59, J_spacer_battery_3_top1.60, P_spacer_battery_3_bot1.30, P_spacer_battery_3_bot1.53, P_spacer_battery_3_bot1.54, P_spacer_battery_3_bot1.55, P_spacer_battery_3_bot1.56, P_spacer_battery_3_bot1.57, P_spacer_battery_3_bot1.58, P_spacer_battery_3_bot1.59, P_spacer_battery_3_bot1.60, SP_battery_3.1
GPIO_EXT_0: J_spacer_battery_3_top1.31, P_spacer_battery_3_bot1.31
GPIO_EXT_1: J_spacer_battery_3_top1.32, P_spacer_battery_3_bot1.32
GPIO_EXT_2: J_spacer_battery_3_top1.33, P_spacer_battery_3_bot1.33
GPIO_EXT_3: J_spacer_battery_3_top1.34, P_spacer_battery_3_bot1.34
H3LIS_INT1: J_spacer_battery_3_top1.35, P_spacer_battery_3_bot1.35
I2C3_SCL: J_spacer_battery_3_top1.36, P_spacer_battery_3_bot1.36
I2C3_SDA: J_spacer_battery_3_top1.37, P_spacer_battery_3_bot1.37
JUMP_WAKE: J_spacer_battery_3_top1.38, P_spacer_battery_3_bot1.38
NRST: J_spacer_battery_3_top1.39, P_spacer_battery_3_bot1.39
SWO: J_spacer_battery_3_top1.40, P_spacer_battery_3_bot1.40
SYS_I2C_SCL: J_spacer_battery_3_top1.41, P_spacer_battery_3_bot1.41
SYS_I2C_SDA: J_spacer_battery_3_top1.42, P_spacer_battery_3_bot1.42
SYS_SPI_CS_FIN: J_spacer_battery_3_top1.43, P_spacer_battery_3_bot1.43
SYS_SPI_MISO: J_spacer_battery_3_top1.44, P_spacer_battery_3_bot1.44
SYS_SPI_MOSI: J_spacer_battery_3_top1.45, P_spacer_battery_3_bot1.45
SYS_SPI_SCLK: J_spacer_battery_3_top1.46, P_spacer_battery_3_bot1.46

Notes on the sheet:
spacer_battery_3

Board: 2 copper layers, 4 parts (1 on the bottom side), 46 nets, no tracks yet.

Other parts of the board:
MH1: smash_mech_potting
